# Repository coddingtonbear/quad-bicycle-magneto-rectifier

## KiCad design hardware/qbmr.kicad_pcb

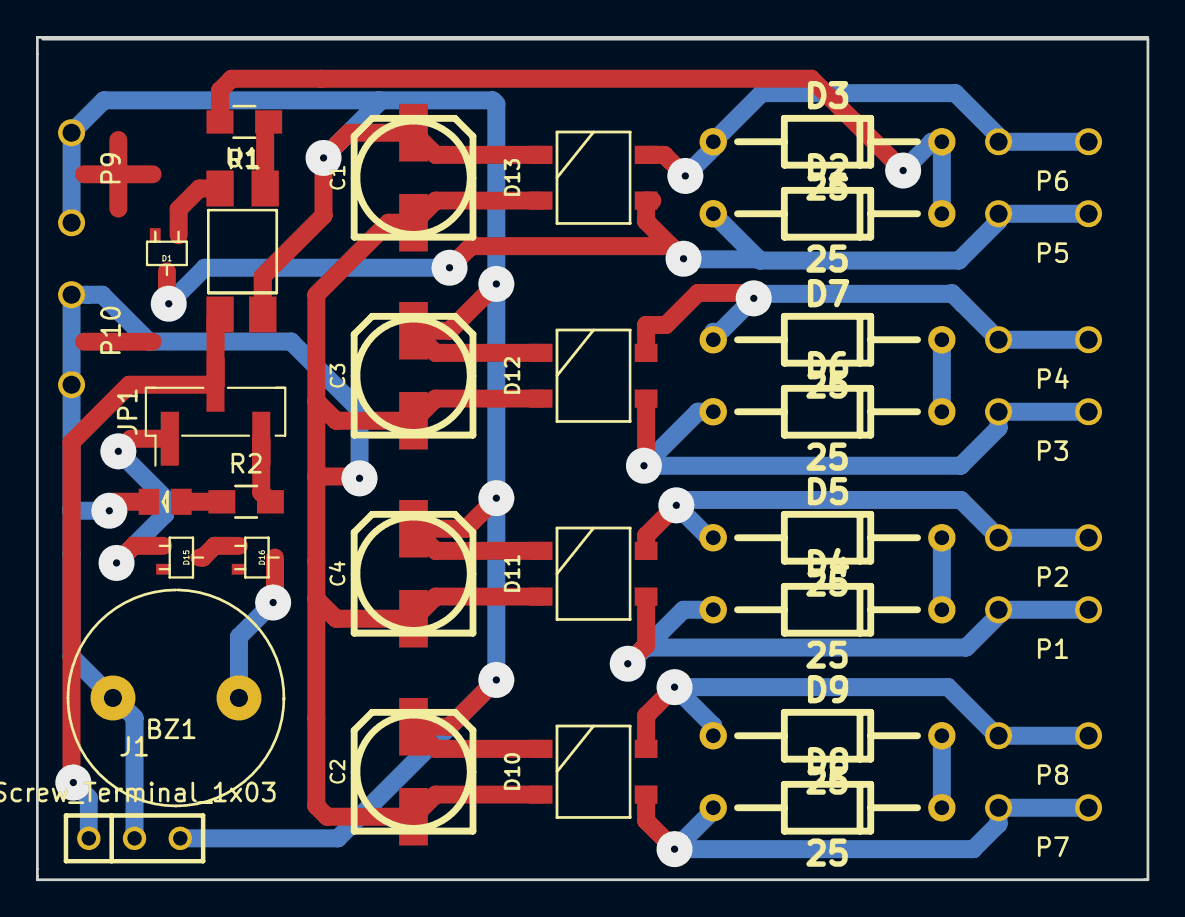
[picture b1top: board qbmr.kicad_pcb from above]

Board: 2 copper layers, 61.7 x 46.8 mm, 36 parts (0 on the bottom side), 22 nets.

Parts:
BZ1: Buzzer; 12mm_buzzer
C1, C2, C3, C4: ?; SMD_PANASONIC_D
D1, D15, D16: D; SOT323_diode
D2, D3, D4, D5, D6, D7, D8, D9: 25; DO204AL_500
D10, D11, D12, D13: MB24S(+); SM-TO-269AA
D14: LED; 0805-LED
J1: Screw_Terminal_1x03; Lerche_3P_2.54mm
JP1: Jumper_NC_Dual; Pin_Header_Straight_1x03_Pitch2.54mm_SMD_Pin1Left
P1, P2, P3, P4, P5, P6, P7, P8: CONN_01X01; TAB
P9: VCC; TAB
P10: GND; TAB
R1: 1k; R_0805_HandSoldering
R2: 500; R_0805_HandSoldering
U1: TLP187; SMD-OPTOCOUPLER

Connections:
GND: BZ1.2, C1.2, C2.2, C3.2, C4.2, D10.2, D11.2, D12.2, D13.2, D14.1, J1.2, P10.1
unnamed: BZ1.1, D16.1
unnamed: D1.1, D2.1, D13.3, P5.1
unnamed: D1.2, U1.3
unnamed: D2.2, D3.2, R1.2
unnamed: D4.2, D5.2
unnamed: D6.2, D7.2
unnamed: D8.2, D9.2
unnamed: D8.1, D10.3, P7.1
unnamed: D9.1, D10.4, P8.1
unnamed: D4.1, D11.3, P1.1
unnamed: D5.1, D11.4, P2.1
unnamed: D6.1, D12.3, P3.1
unnamed: D7.1, D12.4, P4.1
unnamed: D3.1, D13.4, P6.1
unnamed: D14.2, R2.1
unnamed: D15.1, D16.2
unnamed: D15.2, JP1.1
unnamed: J1.1, JP1.2, U1.4
unnamed: JP1.3, R2.2
unnamed: R1.1, U1.1
VCC: C1.1, C2.1, C3.1, C4.1, D10.1, D11.1, D12.1, D13.1, J1.3, P9.1, U1.6

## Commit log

2017-05-24 And so it begins...
2017-05-24 Adding LED to overvoltage alarm.
2017-05-24 Adding a missing part number.
2017-07-17 Finished PCB.
2017-08-11 Updating schematics.
2017-09-02 Switching to use a microcontroller for voltage measurements.
